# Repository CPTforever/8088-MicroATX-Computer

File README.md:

# Insert header here

# Features!
insert features

# Memory Map
Insert memory map

# I/O Port Map
Insert port map

# Rev 1 Mistakes
UART Controller uses system clock instead of external crystal, meaning standard baud rates are
only achievable when system clock uses a UART compatible crystal

PIT Gate 1 does not have a pull up resistor, meaning gate is floating when the external io pin is not connected. (This can be bodged with a radial resistor at least.)

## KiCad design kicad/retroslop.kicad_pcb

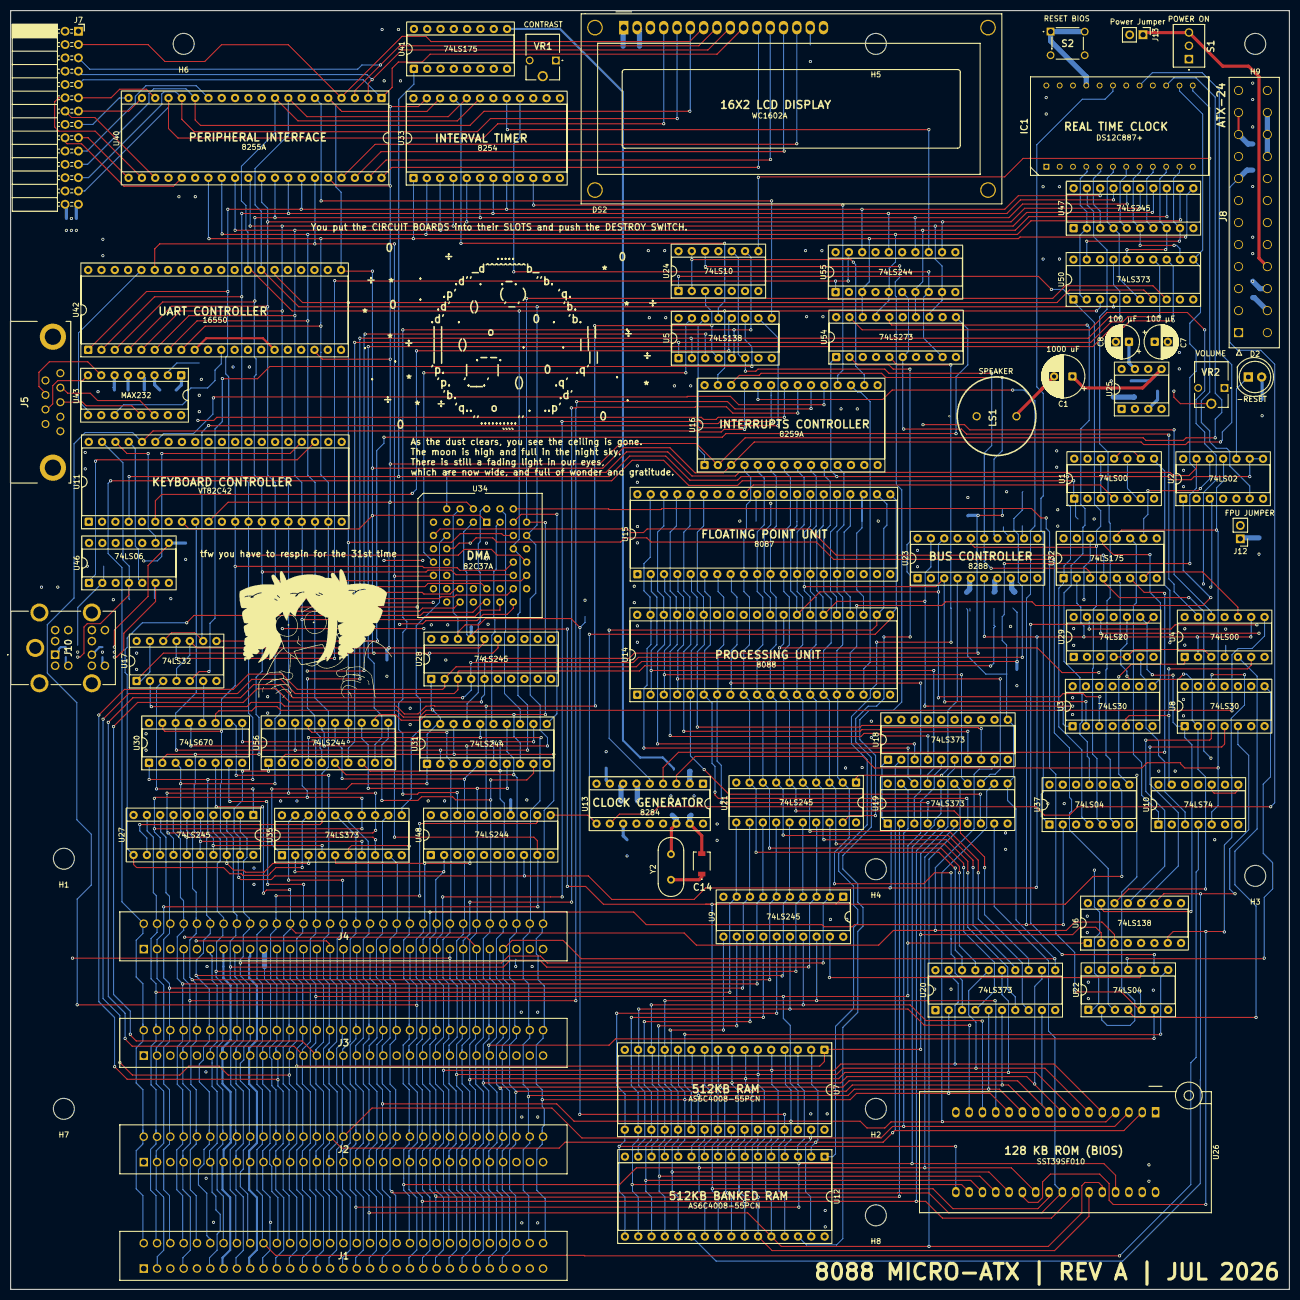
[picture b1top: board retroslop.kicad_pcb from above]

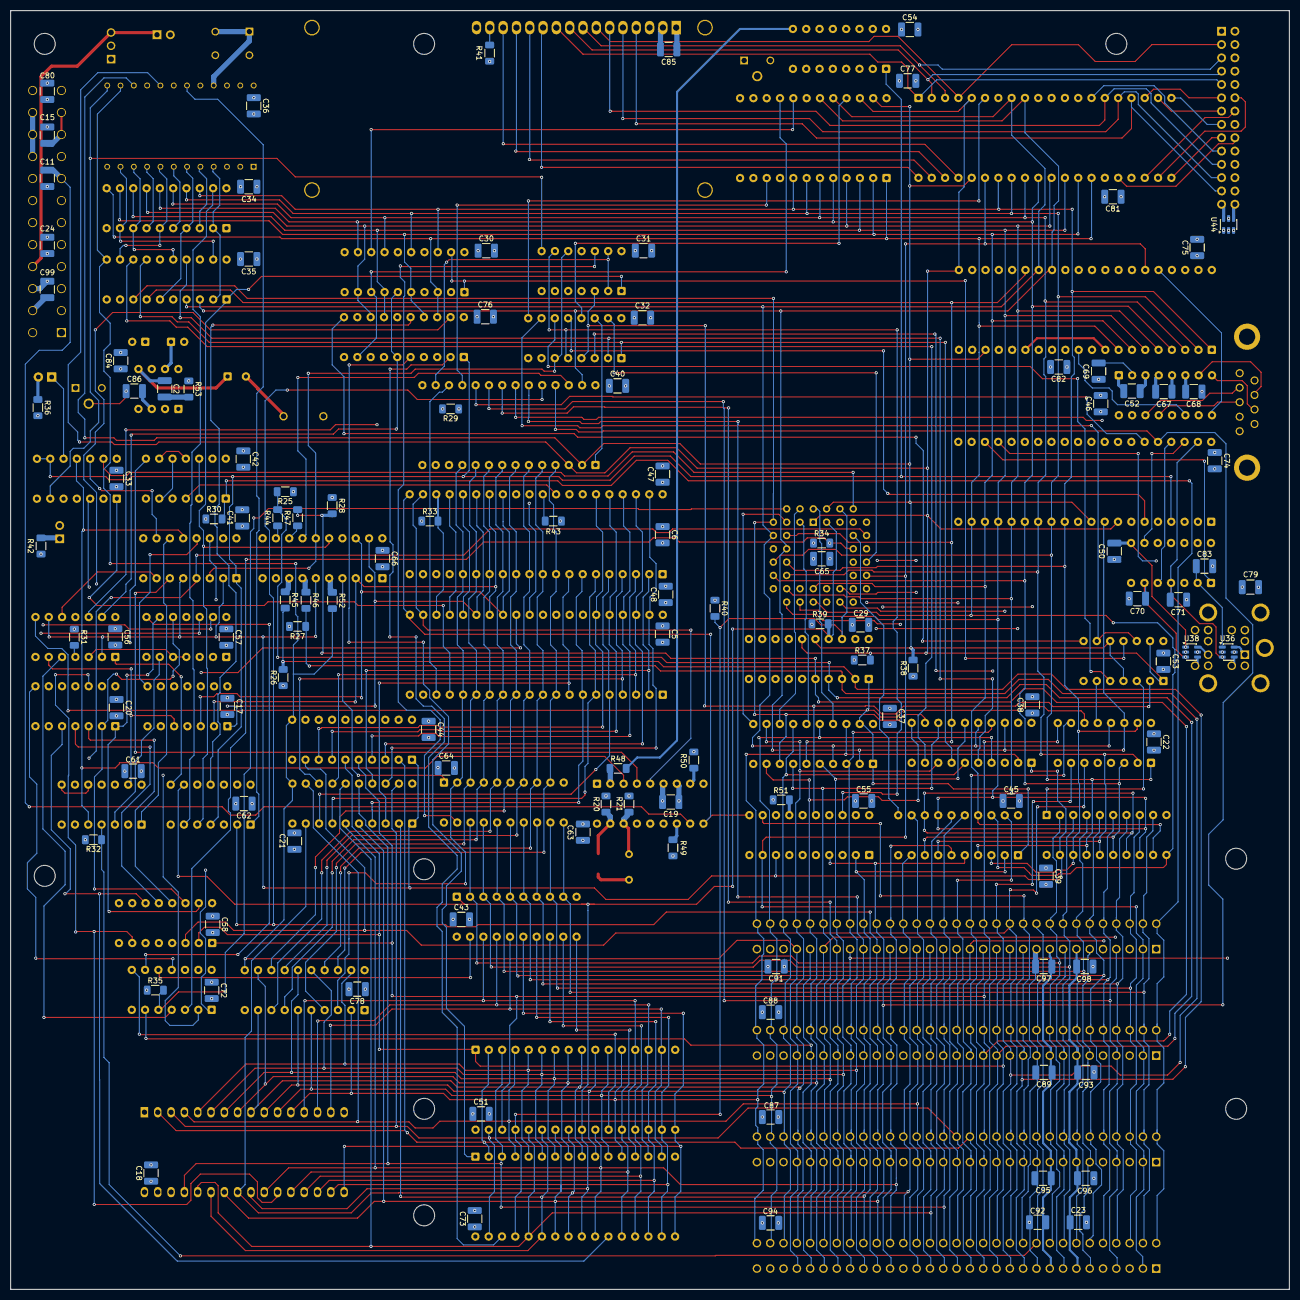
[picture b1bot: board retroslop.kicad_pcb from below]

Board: 6 copper layers, 244.0 x 244.0 mm, 193 parts (114 on the bottom side), 291 nets.

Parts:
C1: 1000 uF; CP_Radial_D8.0mm_P3.50mm
C2: 47 nF; C_1210_3225Metric_Pad1.33x2.70mm_HandSolder
C5, C6: 47nF; C_1210_3225Metric_Pad1.33x2.70mm_HandSolder
C7, C8: 100 μF; CP_Radial_D6.3mm_P2.50mm
C11, C15, C23, C24: 10 uF; C_1210_3225Metric_Pad1.33x2.70mm_HandSolder
C14: JZ300
C17, C18, C19, C20, C21, C22, C29, C30, C31, C32, C33, C34, C35, C36, C37, C38, C39, C40, C41, C42, C43, C44, C45, C46, C47, C48, C51, C53, C54, C55, C56, C57, C58, C61, C62, C63, C64, C65, C66, C72, C73, C74, C75, C76, C77, C78, C79, C80, C81, C82, C84, C85: 0.1 μF; C_1210_3225Metric_Pad1.33x2.70mm_HandSolder
C50, C70, C71, C83: 47 pF; C_1210_3225Metric_Pad1.33x2.70mm_HandSolder
C52, C67, C68, C69, C86: 1 μF; C_1210_3225Metric_Pad1.33x2.70mm_HandSolder
C87, C88, C89, C91, C92, C93, C94, C95, C96, C97, C98, C99: 10 μF; C_1210_3225Metric_Pad1.33x2.70mm_HandSolder
D2: LED; LED_D5.0mm_Clear
DS2: WC1602A
H1, H2, H3, H4, H5, H6, H7, H8, H9: MountingHole; MountingHole_4mm
IC1: DS12C887+; DIP1550W53P254L3378H1042Q24N
J1, J2, J3, J4: Bus_ISA_8bit; 655308435
J5: DE9_Socket; L717SDE09PA4CH4RC309
J7: Conn_02x14_Odd_Even; PinSocket_2x14_P2.54mm_Horizontal
J8: ATX-24; 39-28-1243
J10: KMDGX-6SG_P-S4N; KMDGX6SGPS4N
J12: FPU JUMPER; PinHeader_1x02_P2.54mm_Vertical
J13: Power Jumper; PinHeader_1x02_P2.54mm_Vertical
LS1: CVS-1508
R20, R21: 510 Ω; R_1206_3216Metric_Pad1.30x1.75mm_HandSolder
R25, R26, R27, R28, R29, R30, R31, R32, R33, R34, R35, R37, R38, R39, R40, R42, R43: 4.7k Ω; R_1206_3216Metric_Pad1.30x1.75mm_HandSolder
R36: 220 Ω; R_1206_3216Metric_Pad1.30x1.75mm_HandSolder
R41: 330 Ω; R_1206_3216Metric_Pad1.30x1.75mm_HandSolder
R44, R45, R46, R47, R48, R49, R50, R51, R52: 33 Ω; R_1206_3216Metric_Pad1.30x1.75mm_HandSolder
R53: 10 Ω; R_1206_3216Metric_Pad1.30x1.75mm_HandSolder
S1: Power Switch; 1080041EVX
S2: TS02-66-50-BK-260-SCR-D; TS026650BK260SCRD
U1, U4: 74LS00; DIP-14_W7.62mm_Socket
U2: 74LS02; DIP-14_W7.62mm_Socket
U3, U8: 74LS30; DIP-14_W7.62mm_Socket
U5, U6: 74LS138; DIP-16_W7.62mm_Socket
U7, U12: AS6C4008-55PCN; DIP-32_W15.24mm_Socket
U9, U21, U27, U28, U47: 74LS245; DIP-20_W7.62mm_Socket
U10: 74LS74; DIP-14_W7.62mm_Socket
U11: VT82C42; DIP-40_W15.24mm_Socket
U13: 8284; DIP-18_W7.62mm_Socket
U14: 8088_Max_Mode; DIP-40_W15.24mm_Socket
U15: 8087; DIP-40_W15.24mm_Socket
U16: 8259A; DIP-28_W15.24mm_Socket
U17: 74LS32; DIP-14_W7.62mm_Socket
U18, U19, U20, U35, U50: 74LS373; DIP-20_W7.62mm_Socket
U22, U37: 74LS04; DIP-14_W7.62mm_Socket
U23: 8288; DIP-20_W7.62mm_Socket
U24: 74LS10; DIP-14_W7.62mm_Socket
U25: LM386; DIP-8_W7.62mm_Socket
U26: SST39SF010; DIP_Socket-32_W11.9mm_W12.7mm_W15.24mm_W17.78mm_W18.5mm_3M_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
U29: 74LS20; DIP-14_W7.62mm_Socket
U30: 74LS670; DIP-16_W7.62mm_Socket
U31, U48, U55, U56: 74LS244; DIP-20_W7.62mm_Socket
U32, U41: 74LS175; DIP-16_W7.62mm_Socket
U33: 8254; DIP-24_W15.24mm_Socket
U34: 82C37A; PLCC-44_THT-Socket
U36, U38, U44: USBLC6-2SC6; SOT-23-6
U40: 8255A; DIP-40_W15.24mm_Socket
U42: 16550; DIP-40_W15.24mm_Socket
U43: MAX232; DIP-16_W7.62mm_Socket
U46: 74LS06; DIP-14_W7.62mm_Socket
U54: 74LS273; DIP-20_W7.62mm_Socket
VR1, VR2: N6L30T3N-103-3030; N6L30T3N1033030
Y2: 14.318 MHz; Crystal_HC49-4H_Vertical

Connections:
+5V: C5.1, C6.1, C7.1, C17.1, C18.1, C19.1, C20.1, C21.1, C22.1, C24.1, C29.1, C30.1, C31.1, C32.1, C33.1, C34.1, C35.1, C36.1, C37.1, C38.1, C39.1, C40.1, C41.1, C42.1, C43.1, C44.1, C45.1, C46.1, C47.1, C48.1, C51.1, C53.1, C54.1, C55.1, C56.1, C57.1, C58.1, C61.1, C62.1, C63.1, C64.1, C65.1, C66.1, C72.1, C73.1, C74.1, C75.1, C76.1, C77.1, C78.1, C79.1, C80.1, C81.1, C82.1, C84.1, C85.1, C87.1, C88.1, C91.1, C94.1, DS2.2 (VDD), IC1.18 (~RESET), IC1.24 (VCC), J1.3 (VCC), J1.29 (VCC), J2.3 (VCC), J2.29 (VCC), J3.3 (VCC), J3.29 (VCC), J4.3 (VCC), J4.29 (VCC), J7.2, J8.4 (+5V), J8.6 (+5V), J8.21 (+5V), J8.22 (+5V), J8.23 (+5V), J10.A5, J10.B5, R25.1, R26.1, R27.1, R28.1, R29.1, R30.1, R31.1, R32.1, R33.1, R34.1, R35.1, R36.2, R37.1, R38.1, R39.1, R40.1, R41.1, R42.1, R43.1, U1.14 (VCC), U2.14 (VCC), U3.6, U3.11, U3.12, U3.14 (VCC), U4.14 (VCC), U5.16 (VCC), U6.6 (E3), U6.16 (VCC), U7.32 (VCC), U8.6, U8.11, U8.14 (VCC), U9.20 (VCC), U10.2 (D), U10.14 (VCC), U11.5 (TH_SS), U11.25 (TH_PROG), U11.26 (TH_SSPP), U11.40 (VCC), U12.32 (VCC), U13.7 (~AEN2), U13.18 (VCC), U14.31 (~RQ/~GT0), U14.40 (VCC), U15.33 (~RQ/~GT1), U15.34 (~BHE/S7), U15.40 (VCC), U16.28 (VCC), U17.14 (VCC), U18.20 (VCC), U19.20 (VCC), U20.20 (VCC), U21.20 (VCC), U22.14 (VCC), U23.20 (VCC), U24.4, U24.5, U24.14 (VCC), U25.6 (V+), U26.31 (PGM), U26.32 (VCC), U27.20 (VCC), U28.20 (VCC), U29.14 (VCC), U30.16 (VCC), U31.20 (VCC), U32.16 (VCC), U33.11 (G0), U33.24 (VCC), U34.35 (Vcc), U35.20 (VCC), U36.5 (VBUS), U37.14 (VCC), U38.5 (VBUS), U40.26 (VCC), U41.16 (VCC), U42.12 (CS0), U42.13 (CS1), U42.39 (~RI), U42.40 (VCC), U43.16 (VCC), U44.5 (VBUS), U46.14 (VCC), U47.20 (VCC), U48.20 (VCC), U50.20 (VCC), U54.20 (VCC), U55.20 (VCC), U56.20 (VCC), VR1.3 (CW)
+12V: C15.1, C89.1, C92.1, C95.1, C97.1, J1.9 (+12V), J2.9 (+12V), J3.9 (+12V), J4.9 (+12V), J8.10 (+12V), J8.11 (+12V)
-12V: C23.1, C93.1, C96.1, C98.1, C99.1, J1.7 (-12V), J2.7 (-12V), J3.7 (-12V), J4.7 (-12V), J8.14 (-12V)
/Bus Driver/A0: J1.62 (BA00), J2.62 (BA00), J3.62 (BA00), J4.62 (BA00), U7.12 (A0), U12.12 (A0), U20.2 (O0), U26.12 (A0), U31.18 (O0a), U56.2 (I0a)
/Bus Driver/A1: J1.61 (BA01), J2.61 (BA01), J3.61 (BA01), J4.61 (BA01), U7.11 (A1), U12.11 (A1), U20.5 (O1), U26.11 (A1), U31.16 (O1a), U56.4 (I1a)
/Bus Driver/A2: J1.60 (BA02), J2.60 (BA02), J3.60 (BA02), J4.60 (BA02), U7.10 (A2), U12.10 (A2), U20.6 (O2), U26.10 (A2), U31.14 (O2a), U56.6 (I2a)
/Bus Driver/A3: J1.59 (BA03), J2.59 (BA03), J3.59 (BA03), J4.59 (BA03), U7.9 (A3), U12.9 (A3), U20.9 (O3), U26.9 (A3), U31.12 (O3a), U56.8 (I3a)
/Bus Driver/A4: J1.58 (BA04), J2.58 (BA04), J3.58 (BA04), J4.58 (BA04), U7.8 (A4), U12.8 (A4), U20.12 (O4), U26.8 (A4), U31.9 (O0b), U56.11 (I0b)
/Bus Driver/A5: J1.57 (BA05), J2.57 (BA05), J3.57 (BA05), J4.57 (BA05), U7.7 (A5), U12.7 (A5), U20.15 (O5), U26.7 (A5), U31.7 (O1b), U56.13 (I1b)
/Bus Driver/A6: J1.56 (BA06), J2.56 (BA06), J3.56 (BA06), J4.56 (BA06), U7.6 (A6), U12.6 (A6), U20.16 (O6), U26.6 (A6), U31.5 (O2b), U56.15 (I2b)
/Bus Driver/A7: J1.55 (BA07), J2.55 (BA07), J3.55 (BA07), J4.55 (BA07), U7.5 (A7), U12.5 (A7), U20.19 (O7), U26.5 (A7), U31.3 (O3b), U56.17 (I3b)
/Bus Driver/A8: J1.54 (BA08), J2.54 (BA08), J3.54 (BA08), J4.54 (BA08), U7.27 (A8), U12.27 (A8), U19.2 (O0), U26.27 (A8), U35.2 (O0), U48.2 (I0a)
/Bus Driver/A9: J1.53 (BA09), J2.53 (BA09), J3.53 (BA09), J4.53 (BA09), U7.26 (A9), U12.26 (A9), U19.5 (O1), U26.26 (A9), U35.5 (O1), U48.4 (I1a)
/Bus Driver/A10: J1.52 (BA10), J2.52 (BA10), J3.52 (BA10), J4.52 (BA10), U7.23 (A10), U12.23 (A10), U19.6 (O2), U26.23 (A10), U35.6 (O2)
/Bus Driver/A11: J1.51 (BA11), J2.51 (BA11), J3.51 (BA11), J4.51 (BA11), U7.25 (A11), U12.25 (A11), U19.9 (O3), U26.25 (A11), U35.9 (O3)
/Bus Driver/A12: J1.50 (BA12), J2.50 (BA12), J3.50 (BA12), J4.50 (BA12), U7.4 (A12), U12.4 (A12), U19.12 (O4), U26.4 (A12), U35.12 (O4)
/Bus Driver/A13: J1.49 (BA13), J2.49 (BA13), J3.49 (BA13), J4.49 (BA13), U7.28 (A13), U12.28 (A13), U19.15 (O5), U26.28 (A13), U35.15 (O5)
/Bus Driver/A14: J1.48 (BA14), J2.48 (BA14), J3.48 (BA14), J4.48 (BA14), U7.3 (A14), U12.3 (A14), U19.16 (O6), U26.29 (A14), U35.16 (O6)
/Bus Driver/A15: J1.47 (BA15), J2.47 (BA15), J3.47 (BA15), J4.47 (BA15), U7.31 (A15), U12.31 (A15), U19.19 (O7), U26.3 (A15), U35.19 (O7)
/Bus Driver/A16: J1.46 (BA16), J2.46 (BA16), J3.46 (BA16), J4.46 (BA16), U7.2 (A16), U12.2 (A16), U18.2 (O0), U26.2 (A16), U30.10 (Q1)
/Bus Driver/A17: J1.45 (BA17), J2.45 (BA17), J3.45 (BA17), J4.45 (BA17), U6.1 (A0), U7.30 (A17), U18.5 (O1), U30.9 (Q2)
/Bus Driver/A18: J1.44 (BA18), J2.44 (BA18), J3.44 (BA18), J4.44 (BA18), U6.2 (A1), U7.1 (A18), U18.6 (O2), U30.7 (Q3)
/Bus Driver/A19: J1.43 (BA19), J2.43 (BA19), J3.43 (BA19), J4.43 (BA19), U6.3 (A2), U18.9 (O3), U30.6 (Q4)
/Bus Driver/AEN: J1.42 (AEN), J2.42 (AEN), J3.42 (AEN), J4.42 (AEN), U48.12 (O3a)
/Bus Driver/D0: J1.40 (DB0), J2.40 (DB0), J3.40 (DB0), J4.40 (DB0), U9.2 (A0), U21.18 (B0), U27.2 (A0)
/Bus Driver/D1: J1.39 (DB1), J2.39 (DB1), J3.39 (DB1), J4.39 (DB1), U9.3 (A1), U21.17 (B1), U27.3 (A1)
/Bus Driver/D2: J1.38 (DB2), J2.38 (DB2), J3.38 (DB2), J4.38 (DB2), U9.4 (A2), U21.16 (B2), U27.4 (A2)
/Bus Driver/D3: J1.37 (DB3), J2.37 (DB3), J3.37 (DB3), J4.37 (DB3), U9.5 (A3), U21.15 (B3), U27.5 (A3)
/Bus Driver/D4: J1.36 (DB4), J2.36 (DB4), J3.36 (DB4), J4.36 (DB4), U9.6 (A4), U21.14 (B4), U27.6 (A4)
/Bus Driver/D5: J1.35 (DB5), J2.35 (DB5), J3.35 (DB5), J4.35 (DB5), U9.7 (A5), U21.13 (B5), U27.7 (A5)
/Bus Driver/D6: J1.34 (DB6), J2.34 (DB6), J3.34 (DB6), J4.34 (DB6), U9.8 (A6), U21.12 (B6), U27.8 (A6)
/Bus Driver/D7: J1.33 (DB7), J2.33 (DB7), J3.33 (DB7), J4.33 (DB7), U9.9 (A7), U21.11 (B7), U27.9 (A7)
/Bus Driver/RESET: J1.2 (RESET), J2.2 (RESET), J3.2 (RESET), J4.2 (RESET), U34.15 (RESET), U40.35 (RESET), U42.35 (MR), U48.9 (O0b)
/Bus Driver/RESET BRD: U13.10 (RESET), U14.21 (RESET), U15.21 (RESET), U37.3, U48.11 (I0b)
/Bus Driver/XA0: U11.9 (A0), U16.27 (A0), U30.14 (Wa), U31.2 (I0a), U33.19 (A0), U34.36 (A0), U40.9 (A0), U42.28 (A0), U50.3 (D0), U56.18 (O0a)
/Bus Driver/XA1: U30.13 (Wb), U31.4 (I1a), U33.20 (A1), U34.37 (A1), U40.8 (A1), U42.27 (A1), U50.4 (D1), U56.16 (O1a)
/Bus Driver/XA2: U31.6 (I2a), U34.38 (A2), U42.26 (A2), U50.7 (D2), U56.14 (O2a)
/Bus Driver/XA3: U31.8 (I3a), U34.39 (A3), U50.8 (D3), U56.12 (O3a)
/Bus Driver/XA4: U50.13 (D4), U56.9 (O0b)
/Bus Driver/XA5: U5.1 (A0), U50.14 (D5), U56.7 (O1b)
/Bus Driver/XA6: U5.2 (A1), U50.17 (D6), U56.5 (O2b)
/Bus Driver/XA7: U5.3 (A2), U56.3 (O3b)
/Bus Driver/XA8: U5.5 (E2), U24.9, U48.18 (O0a)
/Bus Driver/XA9: U5.4 (E1), U17.2, U24.3, U48.16 (O1a)
/Bus Driver/XD0: U11.12 (D0), U27.18 (B0), U30.15 (D1), U33.8 (D0), U34.34 (DB0), U35.3 (D0), U40.34 (D0), U42.1 (D0), U47.18 (B0), U54.3 (D0), U55.18 (O0a)
/Bus Driver/XD1: U11.13 (D1), U27.17 (B1), U30.1 (D2), U33.7 (D1), U34.33 (DB1), U35.4 (D1), U40.33 (D1), U42.2 (D1), U47.17 (B1), U54.4 (D1), U55.16 (O1a)
/Bus Driver/XD2: U11.14 (D2), U27.16 (B2), U30.2 (D3), U33.6 (D2), U34.32 (DB2), U35.7 (D2), U40.32 (D2), U42.3 (D2), U47.16 (B2), U54.7 (D2), U55.14 (O2a)
/Bus Driver/XD3: U11.15 (D3), U27.15 (B3), U30.3 (D4), U33.5 (D3), U34.31 (DB3), U35.8 (D3), U40.31 (D3), U42.4 (D3), U47.15 (B3), U54.8 (D3), U55.12 (O3a)
/Bus Driver/XD4: U11.16 (D4), U27.14 (B4), U33.4 (D4), U34.30 (DB4), U35.13 (D4), U40.30 (D4), U42.5 (D4), U47.14 (B4), U54.13 (D4), U55.9 (O0b)
/Bus Driver/XD5: U11.17 (D5), U27.13 (B5), U33.3 (D5), U34.26 (DB5), U35.14 (D5), U40.29 (D5), U42.6 (D5), U47.13 (B5), U54.14 (D5), U55.7 (O1b)
/Bus Driver/XD6: U11.18 (D6), U27.12 (B6), U33.2 (D6), U34.25 (DB6), U35.17 (D6), U40.28 (D6), U42.7 (D6), U47.12 (B6), U54.17 (D6), U55.5 (O2b)
/Bus Driver/XD7: U11.19 (D7), U27.11 (B7), U33.1 (D7), U34.24 (DB7), U35.18 (D7), U40.27 (D7), U42.8 (D7), U47.11 (B7), U54.18 (D7), U55.3 (O3b)
/Bus Driver/~DMA AEN: U4.8, U28.1 (A->B), U30.11 (~Er), U31.1 (OEa), U31.19 (OEb), U35.1 (OE)
/DMA/DA4: U31.11 (I0b), U34.41 (A4)
/DMA/DA5: U31.13 (I1b), U34.42 (A5)
/DMA/DA6: U31.15 (I2b), U34.43 (A6)
/DMA/DA7: U31.17 (I3b), U34.44 (A7)
/DMA/DRQ1: J1.18 (DRQ1), J2.18 (DRQ1), J3.18 (DRQ1), J4.18 (DRQ1), U34.21 (DREQ1)
/DMA/DRQ2: J1.6 (DRQ2), J2.6 (DRQ2), J3.6 (DRQ2), J4.6 (DRQ2), U34.20 (DREQ2)
/DMA/DRQ3: J1.16 (DRQ3), J2.16 (DRQ3), J3.16 (DRQ3), J4.16 (DRQ3), U34.19 (DREQ3)
/DMA/RDY TO DMA: U2.13, U34.6 (READY)
/DMA/Terminal Count: J1.27 (TC), J2.27 (TC), J3.27 (TC), J4.27 (TC), U22.6
/DMA/~DACK0: J1.19 (~DACK0), J2.19 (~DACK0), J3.19 (~DACK0), J4.19 (~DACK0), U34.28 (DACK0)
/DMA/~DACK1: J1.17 (~DACK1), J2.17 (~DACK1), J3.17 (~DACK1), J4.17 (~DACK1), U34.27 (DACK1)
/DMA/~DACK2: J1.26 (~DACK2), J2.26 (~DACK2), J3.26 (~DACK2), J4.26 (~DACK2), U30.4 (Rb), U34.16 (DACK2)
/DMA/~DACK3: J1.15 (~DACK3), J2.15 (~DACK3), J3.15 (~DACK3), J4.15 (~DACK3), U30.5 (Ra), U34.18 (DACK3)
/DMA/~HRQ DMA: U4.5, U22.4
/Device Decoder/~AEN: U5.6 (E3), U23.15 (CEN), U24.10, U32.3 (~Q0)
/Device Decoder/~MEM_ADDR_SEL: U9.19 (CE), U22.10
/Device Decoder/~PIC CS: U5.14 (O1), U16.1 (~CS)
/Device Decoder/~RAM_BANK_CS: U6.11 (O4), U8.5, U12.22 (CE#)
/Device Decoder/~RAM_CS: U7.22 (CE#), U22.8
/Device Decoder/~ROM_CS: U6.7 (O7), U8.12, U26.22 (CE)
/Flag Registers/ALLOW NMI: U22.13, U54.19 (Q7), U55.17 (I3b)
/Flag Registers/BA0: U12.30 (A17), U54.2 (Q0), U55.2 (I0a)
/Flag Registers/BA1: U12.1 (A18), U54.5 (Q1), U55.4 (I1a)
/Flag Registers/ENABLE IO CK: U37.11, U54.16 (Q6), U55.15 (I2b)
/Flag Registers/I/O CH CK: U1.3, U1.12, U55.11 (I0b)
/Flag Registers/SPKR EN: U4.13, U54.6 (Q2), U55.6 (I2a)
/Flag Registers/SPKR GATE: U33.16 (G2), U54.9 (Q3), U55.8 (I3a)
/Flag Registers/SPKR OUT: U4.12, U33.17 (OUT2), U55.13 (I1b)
/ISA BUS/I/O CH RDY: J1.41 (IO_READY), J2.41 (IO_READY), J3.41 (IO_READY), J4.41 (IO_READY), R32.2, U10.4 (~S)
/ISA BUS/~HRQ I/O CH: J1.8 (UNUSED), J2.8 (UNUSED), J3.8 (UNUSED), J4.8 (UNUSED)
/ISA BUS/~I/O CH CK: J1.32 (IO), J2.32 (IO), J3.32 (IO), J4.32 (IO), R30.2, U1.1
/Keyboard/KEYBOARD CLOCK: C70.1, U11.1 (TEST0), U38.3 (I/O2), U46.6
/Keyboard/KEYBOARD DATA: C50.1, U11.27 (P10), U38.1 (I/O1), U46.8
/Keyboard/MOUSE CLOCK: C71.1, U11.39 (TEST1), U36.3 (I/O2), U46.4
/Keyboard/MOUSE DATA: C83.1, U11.28 (P11), U36.1 (I/O1), U46.2
/POWER/PWR GOOD: C11.1, J8.8 (PWR_OK), U13.11 (~RES)
/Pinout/PA0: DS2.7 (D0), J7.3, U40.4 (PA0)
/Pinout/PA1: DS2.8 (D1), J7.5, U40.3 (PA1)
/Pinout/PA2: DS2.9 (D2), J7.7, U40.2 (PA2)
/Pinout/PA3: DS2.10 (D3), J7.9, U40.1 (PA3)
/Pinout/PA4: DS2.11 (D4), J7.4, U40.40 (PA4)
/Pinout/PA5: DS2.12 (D5), J7.6, U40.39 (PA5)
/Pinout/PA6: DS2.13 (D6), J7.8, U40.38 (PA6)
/Pinout/PA7: DS2.14 (D7), J7.10, U40.37 (PA7)
/Pinout/PB0: J7.11, U40.18 (PB0)
/Pinout/PB1: J7.13, U40.19 (PB1)
/Pinout/PB2: J7.15, U40.20 (PB2)
/Pinout/PB3: J7.17, U40.21 (PB3)
/Pinout/PB4: J7.12, U40.22 (PB4)
/Pinout/PB5: J7.14, U40.23 (PB5)
/Pinout/PB6: J7.16, U40.24 (PB6)
/Pinout/PB7: J7.18, U40.25 (PB7)
/Pinout/PC0: J7.19, U40.14 (PC0)
/Pinout/PC1: DS2.6 (E), J7.21, U40.15 (PC1)
/Pinout/PC2: DS2.5 (R/W), J7.23, U40.16 (PC2)
/Pinout/PC3: DS2.4 (RS), J7.25, U40.17 (PC3)
/Pinout/PC4: J7.20, U40.13 (PC4)
/Pinout/PC5: J7.22, U40.12 (PC5)
/Pinout/PC6: J7.24, U40.11 (PC6)
/Pinout/PC7: J7.26, U40.10 (PC7)
/Pinout/PIT GATE: U33.14 (G1), U44.3 (I/O2)
/Pinout/PIT OUT: U33.13 (OUT1), U44.1 (I/O1)
/Processor And Control/AX0: U14.16 (AD0), U15.16 (AD0), U16.11 (D0), U20.3 (D0), U21.2 (A0)
/Processor And Control/AX1: U14.15 (AD1), U15.15 (AD1), U16.10 (D1), U20.4 (D1), U21.3 (A1)
/Processor And Control/AX2: U14.14 (AD2), U15.14 (AD2), U16.9 (D2), U20.7 (D2), U21.4 (A2)
/Processor And Control/AX3: U14.13 (AD3), U15.13 (AD3), U16.8 (D3), U20.8 (D3), U21.5 (A3)
/Processor And Control/AX4: U14.12 (AD4), U15.12 (AD4), U16.7 (D4), U20.13 (D4), U21.6 (A4)
/Processor And Control/AX5: U14.11 (AD5), U15.11 (AD5), U16.6 (D5), U20.14 (D5), U21.7 (A5)
/Processor And Control/AX6: U14.10 (AD6), U15.10 (AD6), U16.5 (D6), U20.17 (D6), U21.8 (A6)
/Processor And Control/AX7: U14.9 (AD7), U15.9 (AD7), U16.4 (D7), U20.18 (D7), U21.9 (A7)
/Processor And Control/AX8: U14.8 (A8), U15.8 (AD8), U19.3 (D0)
/Processor And Control/AX9: U14.7 (A9), U15.7 (AD9), U19.4 (D1)
/Processor And Control/AX10: U14.6 (A10), U15.6 (AD10), U19.7 (D2)
/Processor And Control/AX11: U14.5 (A11), U15.5 (AD11), U19.8 (D3)
/Processor And Control/AX12: U14.4 (A12), U15.4 (AD12), U19.13 (D4)
/Processor And Control/AX13: U14.3 (A13), U15.3 (AD13), U19.14 (D5)
/Processor And Control/AX14: U14.2 (A14), U15.2 (AD14), U19.17 (D6)
/Processor And Control/AX15: U14.39 (A15), U15.39 (AD15), U19.18 (D7)
/Processor And Control/AX16: U14.38 (A16/S3), U15.38 (A16/S3), U18.3 (D0)
/Processor And Control/AX17: U14.37 (A17/S4), U15.37 (A17/S4), U18.4 (D1)
/Processor And Control/AX18: U14.36 (A18/S5), U15.36 (A18/S5), U18.7 (D2)
/Processor And Control/AX19: U14.35 (A19/S6), U15.35 (A19/S6), U18.8 (D3)
/Processor And Control/FPU IRQ: U1.4, U15.32 (INT)
/Processor And Control/IRQ0: U16.18 (IR0), U33.10 (OUT0)
/Processor And Control/IRQ1: U11.35 (P24), U16.19 (IR1)
/Processor And Control/IRQ2: J1.4 (IRQ2), J2.4 (IRQ2), J3.4 (IRQ2), J4.4 (IRQ2), U16.20 (IR2)
/Processor And Control/IRQ3: J1.25 (IRQ3), J2.25 (IRQ3), J3.25 (IRQ3), J4.25 (IRQ3), U16.21 (IR3)
/Processor And Control/IRQ4: J1.24 (IRQ4), J2.24 (IRQ4), J3.24 (IRQ4), J4.24 (IRQ4), U16.22 (IR4), U42.30 (INTR)
/Processor And Control/IRQ5: J1.23 (IRQ5), J2.23 (IRQ5), J3.23 (IRQ5), J4.23 (IRQ5), U16.23 (IR5)
/Processor And Control/IRQ6: J1.22 (IRQ6), J2.22 (IRQ6), J3.22 (IRQ6), J4.22 (IRQ6), U16.24 (IR6), U37.2
/Processor And Control/IRQ7: J1.21 (IRQ7), J2.21 (IRQ7), J3.21 (IRQ7), J4.21 (IRQ7), U11.36 (P25), U16.25 (IR7)
/Processor And Control/NMI: U2.1, U14.17 (NMI)
/Processor And Control/QS1: U14.24 (QS1), U15.24 (QS1)
/Processor And Control/QSO: U14.25 (QS0), U15.25 (QS0)
/Processor And Control/~DMA WAIT: U13.4 (RDY1), U32.6 (~Q1)
/Processor And Control/~LOCK: U3.4, U14.29 (~LOCK)
/Processor And Control/~S0: U3.1, U14.26 (~S0), U15.26 (~S0), U23.19 (~S0)
/Processor And Control/~S1: U3.2, U14.27 (~S1), U15.27 (~S1), U23.3 (~S1)
/Processor And Control/~S2: U3.3, U14.28 (~S2), U15.28 (~S2), U23.18 (~S2)
/RAM and ROM/MD0: U7.13 (DQ0), U9.18 (B0), U12.13 (DQ0), U26.13 (D0)
/RAM and ROM/MD1: U7.14 (DQ1), U9.17 (B1), U12.14 (DQ1), U26.14 (D1)
/RAM and ROM/MD2: U7.15 (DQ2), U9.16 (B2), U12.15 (DQ2), U26.15 (D2)
/RAM and ROM/MD3: U7.17 (DQ3), U9.15 (B3), U12.17 (DQ3), U26.17 (D3)
/RAM and ROM/MD4: U7.18 (DQ4), U9.14 (B4), U12.18 (DQ4), U26.18 (D4)
/RAM and ROM/MD5: U7.19 (DQ5), U9.13 (B5), U12.19 (DQ5), U26.19 (D5)
/RAM and ROM/MD6: U7.20 (DQ6), U9.12 (B6), U12.20 (DQ6), U26.20 (D6)
/RAM and ROM/MD7: U7.21 (DQ7), U9.11 (B7), U12.21 (DQ7), U26.21 (D7)
/RTC/AD0: IC1.4 (AD0), U47.2 (A0), U50.2 (O0)
/RTC/AD1: IC1.5 (AD1), U47.3 (A1), U50.5 (O1)
/RTC/AD2: IC1.6 (AD2), U47.4 (A2), U50.6 (O2)
/RTC/AD3: IC1.7 (AD3), U47.5 (A3), U50.9 (O3)
/RTC/AD4: IC1.8 (AD4), U47.6 (A4), U50.12 (O4)
/RTC/AD5: IC1.9 (AD5), U47.7 (A5), U50.15 (O5)
/RTC/AD6: IC1.10 (AD6), U47.8 (A6), U50.16 (O6)
/RTC/AD7: IC1.11 (AD7), U47.9 (A7), U50.19 (O7)
/RTC/ADDR EN: U23.16 (DEN), U24.1, U37.5, U50.1 (OE)
/RTC/ADDR LATCH: IC1.14 (AS), J1.28 (ALE), J2.28 (ALE), J3.28 (ALE), J4.28 (ALE), R52.2, U18.11 (LE), U19.11 (LE), U20.11 (LE), U50.11 (LE)
/RTC/DATA EN: U37.6, U47.19 (CE)
/RTC/RTC DIR: U2.4, U47.1 (A->B)
/UART/CTS: J5.8, U43.8 (R2IN)
/UART/RTS: J5.7, U43.7 (T2OUT)
/UART/RXD: J5.2, U43.14 (T1OUT)
/UART/TXD: J5.3, U43.13 (R1IN)
/Wait State Generator/AEN: U4.2, U4.9, U18.1 (OE), U19.1 (OE), U20.1 (OE), U23.6 (~AEN), U27.19 (CE), U32.2 (Q0), U32.5 (D1), U48.8 (I3a), U56.1 (OEa), U56.19 (OEb)
/Wait State Generator/DMA WAIT: U4.10, U32.7 (Q1)
/Wait State Generator/FPU INSTL: J12.1, R42.2, U1.5
/Wait State Generator/HOLDA: U10.9 (Q), U32.4 (D0), U34.9 (HLDA)
/Wait State Generator/RDY/~WAIT DLY: U10.1 (~R), U32.11 (~Q2)
/Wait State Generator/~CLK: U10.11 (C), U37.12
/Wait State Generator/~ENABLE IO CK: U1.13, U37.10
/Wait State Generator/~RDY/WAIT: U2.11, U10.5 (Q), U13.3 (~AEN1), U32.12 (D2)
/Wait State Generator/~RDY/WAIT DLY: U2.12, U32.10 (Q2)
/Wait State Generator/~RESET: U2.8, U2.9, U11.4 (~RESET), U32.1 (~Mr), U37.4, U41.1 (~Mr), U54.1 (~Mr)
/~CS0: U5.15 (O0), U34.13 (~CS)
/~CS1: U5.13 (O2), U33.21 (~CS)
/~CS2: U5.12 (O3), U11.6 (~CS)
/~CS3: U5.11 (O4), U17.5
/~CS4: U5.10 (O5), U17.9, U17.12
/~CS5: U5.9 (O6), U40.6 (~CS)
/~CS6: U5.7 (O7), U42.14 (~CS2)
/~CS7: IC1.13 (~CS), U2.6, U24.8
/~IOR: J1.14 (~IOR), J2.14 (~IOR), J3.14 (~IOR), J4.14 (~IOR), R28.2, R47.2, U28.5 (A3)
/~IOW: J1.13 (~IOW), J2.13 (~IOW), J3.13 (~IOW), J4.13 (~IOW), R25.2, R44.2, U28.4 (A2)
/~MEMR: J1.12 (~SMEMR), J2.12 (~SMEMR), J3.12 (~SMEMR), J4.12 (~SMEMR), R27.2, R46.2, U28.3 (A1)
/~MEMW: J1.11 (~SMEMW), J2.11 (~SMEMW), J3.11 (~SMEMW), J4.11 (~SMEMW), R26.2, R45.2, U28.2 (A0)
/~XIOR: IC1.17 (DS), R37.2, U2.5, U11.8 (~RD), U16.3 (~RD), U17.1, U17.13, U28.15 (B3), U29.1, U33.22 (~RD), U34.1 (~IOR), U40.5 (~RD), U42.21 (~RD)
/~XIOW: IC1.15 (R/~W), R38.2, U11.10 (~WR), U16.2 (~WR), U17.4, U17.10, U28.16 (B2), U29.2, U33.23 (~WR), U34.2 (~IOW), U40.36 (~WR), U42.18 (~WR)
/~XMEMR: R39.2, U7.24 (OE#), U9.1 (A->B), U12.24 (OE#), U26.24 (OE), U28.17 (B1), U34.3 (~MEMR), U37.9
/~XMEMW: R40.2, U7.29 (WE#), U12.29 (WE#), U28.18 (B0), U34.4 (~MEMW)
CLK: J1.20 (CLK), J2.20 (CLK), J3.20 (CLK), J4.20 (CLK), R51.2, U11.3 (XTAL_2), U23.2 (CLK), U32.9 (Cp), U34.14 (CLK), U42.16 (XIN)
CLK88: R50.2, U14.19 (CLK), U15.19 (CLK), U37.13, U48.6 (I2a)
GND: C5.2, C6.2, C7.2, C8.2, C11.2, C15.2, C17.2, C18.2, C19.2, C20.2, C21.2, C22.2, C23.2, C24.2, C29.2, C30.2, C31.2, C32.2, C33.2, C34.2, C35.2, C36.2, C37.2, C38.2, C39.2, C40.2, C41.2, C42.2, C43.2, C44.2, C45.2, C46.2, C47.2, C48.2, C50.2, C51.2, C53.2, C54.2, C55.2, C56.2, C57.2, C58.2, C61.2, C62.2, C63.2, C64.2, C65.2, C66.2, C68.2, C69.2, C70.2, C71.2, C72.2, C73.2, C74.2, C75.2, C76.2, C77.2, C78.2, C79.2, C80.2, C81.2, C82.2, C83.2, C84.2, C85.2, C87.2, C88.2, C89.2, C91.2, C92.2, C93.2, C94.2, C95.2, C96.2, C97.2, C98.2, C99.2, DS2.1 (VSS), DS2.16 (LED(-)), IC1.12 (GND), J1.1 (GND), J1.10 (GND), J1.31 (GND), J2.1 (GND), J2.10 (GND), J2.31 (GND), J3.1 (GND), J3.10 (GND), J3.31 (GND), J4.1 (GND), J4.10 (GND), J4.31 (GND), J5.5, J5.MH1, J5.MH2, J7.1, J8.3 (GND), J8.5 (GND), J8.7 (GND), J8.15 (GND), J8.17 (GND), J8.18 (GND), J8.19 (GND), J8.24 (GND), J10.A3, J10.B3, J10.MH1, J10.MH2, J10.MH3, J10.MH4, J10.MH5, J12.2, J13.2, LS1.1 (-), R20.2, R21.2, R53.2, S1.1 (NC), S1.2 (NOT_CONNECTED), S2.3 (COM_1), S2.4 (COM_2), U1.7 (GND), U2.7 (GND), U3.7 (GND), U4.7 (GND), U5.8 (GND), U6.4 (E1), U6.5 (E2), U6.8 (GND), U7.16 (VSS), U8.7 (GND), U9.10 (GND), U10.7 (GND), U11.2 (XTAL_1), U11.7 (TL_EA), U11.20 (GND), U12.16 (VSS), U13.1 (CSYNC), U13.6 (RDY2), U13.9 (GND), U13.13 (F/~C), U13.15 (~ASYNC), U14.1 (GND), U14.20 (GND), U14.33 (MN/~MX), U15.1 (GND), U15.20 (GND), U16.14 (GND), U17.7 (GND), U18.10 (GND), U18.13 (D4), U18.14 (D5), U18.17 (D6), U18.18 (D7), U19.10 (GND), U20.10 (GND), U21.10 (GND), U22.7 (GND), U23.1 (IOB), U23.10 (GND), U24.7 (GND), U25.2 (-), U25.4 (GND), U26.16 (GND), U27.10 (GND), U28.10 (GND), U28.19 (CE), U29.7 (GND), U30.8 (GND), U31.10 (GND), U32.8 (GND), U33.12 (GND), U34.22 (DREQ0), U34.23 (GND), U35.10 (GND), U36.2 (GND), U37.7 (GND), U38.2 (GND), U40.7 (GND), U41.5 (D1), U41.8 (GND), U41.12 (D2), U41.13 (D3), U42.19 (WR), U42.20 (GND), U42.22 (RD), U42.25 (~ADS), U43.15 (GND), U44.2 (GND), U46.7 (GND), U46.11, U46.13, U47.10 (GND), U48.1 (OEa), U48.10 (GND), U48.13 (I1b), U48.15 (I2b), U48.17 (I3b), U48.19 (OEb), U50.10 (GND), U50.18 (D7), U54.10 (GND), U55.10 (GND), U56.10 (GND), VR1.1 (CCW), VR2.3 (CW)
unnamed: C1.1, C2.1, U25.5
unnamed: C2.2, R53.1
unnamed: C14.2 (COLD(ROTOR)_TERMINAL), R20.1, U13.17 (X1)
unnamed: C14.1 (HOT-END_TERMINAL), Y2.2
unnamed: D2.2 (A), R36.1
unnamed: D2.1 (K), U2.10
unnamed: DS2.15 (LED(+)), R41.2
unnamed: DS2.3 (VO), VR1.2 (WIPER)
unnamed: IC1.21 (N.C._(~RCLR)), S2.1 (NO_1), S2.2 (NO_2)
unnamed: IC1.19 (~IRQ), U37.1
unnamed: J7.27, U44.6 (I/O1)
unnamed: J7.28, U44.4 (I/O2)
unnamed: J10.A1, U36.6 (I/O1)
unnamed: J10.A6, U36.4 (I/O2)
unnamed: J10.B1, U38.6 (I/O1)
unnamed: J10.B6, U38.4 (I/O2)
unnamed: J8.16 (PS_ON#), J13.1, S1.3 (COM)
unnamed: C1.2, LS1.2 (+)
unnamed: R31.2, U4.4
unnamed: U1.8, U22.1
unnamed: U1.6, U1.10
unnamed: U1.2, U1.9, U1.11
unnamed: U2.2, U22.2
unnamed: U2.3, U22.12
unnamed: U6.15 (O0), U8.1, U29.9
unnamed: U6.14 (O1), U8.2, U29.10
unnamed: U6.13 (O2), U8.3, U29.12
unnamed: U6.12 (O3), U8.4, U29.13
unnamed: U10.3 (C), U29.6
unnamed: U10.12 (D), U32.14 (~Q3)
unnamed: U10.8 (~Q), U10.10 (~S)
unnamed: U3.5, U4.6, U10.13 (~R)
unnamed: U11.23 (P22), U46.1
unnamed: U11.24 (P23), U46.3
unnamed: U11.37 (P26), U46.5
unnamed: U11.38 (P27), U46.9
unnamed: R50.1, U13.8 (CLK)
unnamed: R49.1, U13.12 (OSC)
unnamed: R48.1, U13.2 (PCLK)
unnamed: U13.5 (READY), U14.22 (READY), U15.22 (READY)
unnamed: R21.1, U13.16 (X2), Y2.1
unnamed: U14.18 (INTR), U16.17 (INT)
unnamed: R43.2, U14.30 (~RQ/~GT1), U15.31 (~RQ/~GT0)
unnamed: R33.2, U14.23 (~TEST), U15.23 (BUSY)
unnamed: U16.26 (~INTA), U23.14 (~INTA)
unnamed: R29.2, U16.16 (~SP/~EN), U24.2, U24.13
unnamed: U21.1 (A->B), U23.4 (DT/~R)
unnamed: U21.19 (CE), U24.12
unnamed: U22.9, U29.8
unnamed: U8.8, U22.11
unnamed: R52.1, U23.5 (ALE)
unnamed: R44.1, U23.12 (~AIOWC)
unnamed: R45.1, U23.8 (~AMWC)
unnamed: R47.1, U23.13 (~IORC)
unnamed: R46.1, U23.7 (~MRDC)
unnamed: U24.6, U24.11
unnamed: C86.2, U25.3 (+)
unnamed: C8.1, U25.7 (BYPASS)
unnamed: U17.3, U27.1 (A->B)
unnamed: U4.3, U29.4, U29.5
unnamed: U17.6, U30.12 (~Ew)
unnamed: U3.8, U32.13 (D3)
unnamed: U33.9 (CLK0), U33.15 (CLK1), U33.18 (CLK2), U41.2 (Q0)
unnamed: U34.10 (ADSTB), U35.11 (LE)
unnamed: R34.2, U22.3, U34.12 (HRQ)
unnamed: R35.2, U22.5, U34.40 (~EOP)
unnamed: U4.1, U37.8
unnamed: U41.3 (~Q0), U41.4 (D0)
unnamed: U42.9 (RCLK), U42.15 (~BAUDOUT)
unnamed: U42.10 (SIN), U43.12 (R1OUT)
unnamed: U42.11 (SOUT), U43.11 (T1IN)
unnamed: U42.36 (~CTS), U43.9 (R2OUT)
unnamed: U42.32 (~RTS), U43.10 (T2IN)
unnamed: C52.1, U43.1 (C1+)
unnamed: C52.2, U43.3 (C1-)
unnamed: C67.1, U43.4 (C2+)
unnamed: C67.2, U43.5 (C2-)
unnamed: C69.1, U43.2 (VS+)
unnamed: C68.1, U43.6 (VS-)
unnamed: R51.1, U48.14 (O2a)
unnamed: U17.8, U54.11 (Cp)
unnamed: U17.11, U55.1 (OEa), U55.19 (OEb)
unnamed: U4.11, VR2.1 (CCW)
unnamed: C86.1, VR2.2 (WIPER)
OSC: J1.30 (OSC), J2.30 (OSC), J3.30 (OSC), J4.30 (OSC), R49.2
PCLK: R48.2, U41.9 (Cp)
